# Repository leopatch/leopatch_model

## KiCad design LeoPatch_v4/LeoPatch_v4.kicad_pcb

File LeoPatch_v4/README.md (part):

# LeoPatch v4 – PCB (KiCad 9)

Newborn CCHD ECG screening board with **two ECG front ends side by side**, so they can be compared on the same hardware: the MAX30003 (digital, SPI) from v3 and the AD8232 (analog, SparkFun circuit) from v2. Each chip has its **own electrode jack**. Plug the lead cable into the jack of the chip you want to test. Do not put two sets of electrodes from both jacks on the same baby at once: the AD8232 drives RL, and the two input circuits would load each other.

4-layer, **70 × 71 mm** (v3 was 70 × 45; the board grew 26 mm at the bottom to make room for the AD8232 block and its jack). Top edge has the 20 × 6.6 mm cut-out under the module's antenna.

- **MCU:** Fanstel BM20BC module (nRF54LM20B + Axon NPU, BLE, 32 MHz and 32.768 kHz crystals built in). Its antenna hangs over the cut-out in the top edge. Keep the battery pack, cables and other metal away from that edge (Fanstel: 30 mm for best range)
- **ECG front end A – MAX30003 (U201, sheet "ECG front end"):** two-electrode lead I (ECGP = LA, ECGN = RA), 1.8 V from U202 (MCP1700T-1802E/TT in v4: the MCP1703AT-1802E/CB had 3 pcs at LCSC; same SOT-23 pinout), 32.768 kHz clock from X201, SPI to the module. Jack **J201 on the left edge** (plug goes in from the left), backup solder header J202. Silkscreen "MAX30003"
  - Input network matches Analog Devices' MAX30003WING2 evaluation kit (checked against it and the MAX30003 datasheet Rev 3): R201 / R202 49.9 kΩ pulse-proof 1206 (eval kit R4/R5 49.9k; Vishay CRCW…HP), C201 1 nF C0G across ECGP–ECGN (eval kit C10), C213 / C214 10 pF C0G from each input to GND (eval kit C8/C11), R208 499 kΩ from VCM to the RL electrode (eval kit R6: biases the baby at the chip's mid-voltage)
  - C202 (CAPP–CAPN) is 1 µF X7R: 0.5 Hz analog high-pass (datasheet default and eval kit C9), settles in ~1–2 s after the electrodes go on – fits the 2–5 s recordings
  - Firmware must close the input switches (clear OPENP / OPENN in CNFG_EMUX, they power up open). Internal lead bias (EN_RBIAS) is optional now that R208 drives RL from VCM; try with and without. SPI mode 0 or 3, ≤ 12 MHz. The part is rated 0–70 °C
- **ECG front end B – AD8232 (U601, sheet "ECG AD8232"):** the v2 circuit (SparkFun SEN-12650 / AD8232 datasheet Fig. 66 with a wider filter): band 0.5 Hz – ~145 Hz, gain ~200, clips at about ±7.8 mV at the electrodes. Jack **J601 on the bottom edge**, backup header J602, test pad TP601 ("ECG") on the op-amp output. Silkscreen "AD8232". Checked against the AD8232 datasheet (Rev D) in v4: R603 / R604 are 360 kΩ (patient current < 10 µA even in a fault: R ≥ 3.3 V / 10 µA, p. 21 and 26; was 180 k), and the output goes OUT → R623 1 kΩ → ECG_OUT with C608 10 nF to GND (p. 26 Fig. 61: the slow op amp needs a charge reservoir for the nRF54 ADC). SDN is only pulled up (R615): the AD8232 is always on. The reference (REFIN, 10 M / 10 M / 100 nF) takes ~2.5 s to settle after power-up
- Both jacks: 3.5 mm TRS, Tip = RL, Ring = LA, Sleeve = RA (same cable for both). Headers: pin 1 RL, 2 LA, 3 RA
- **External flash:** GD25WQ64ESIGR 8 MB SPI/QSPI NOR (U2, C4) on P2.00–P2.05, same pins as the nRF54LM20 DK flash. R2 (100 k) pulls FLASH_CS high. **v4 fix:** this part number is the 208-mil SOP-8 (the S in ESIGR); v2/v3 had a 150-mil SOIC-8 footprint it would not fit. U2 now uses SOIC-8 5.3 × 5.3 mm
- **Power:** 4×AA → on/off → BAT54J → MCP1703A 3.3 V LDO; USB-C 5 V also feeds the LDO through D102. Alligator-clip pins J103 **VIN** (3.6–6 V after the diodes, bypasses the on/off switch), J104 **3V3** (to feed 3.3 V in from a bench supply, or to measure current across JP101, desolder R101 first: R101 0 Ω is in parallel with JP101 and links the regulator to the 3.3 V rail), J105 **GND**
- **USB-C:** USB 2.0 device to the nRF54LM20B (firmware updates after the bootloader is flashed, data export, 5 V power). D+/D- top layer only, length-matched
- **UI:** PASS / CHECK / FAIL LEDs (green / yellow / red), START and EXPORT buttons, small RESET button (SW303). R301 (green LED) is 100 Ω: a green InGaN LED needs ~3 V, so 1 k from a 3.3 V pin gave only ~0.2 mA
- **Status LEDs (v4):** D103 **PWR** (green, on whenever the 3.3 V rail is up, ~0.5 mA) next to the 3V3 pin; a **LEADS ON** panel bottom right with D201 (MAX30003) and D601 (AD8232), green, active high. Firmware lights D201 while the MAX30003 reports no lead-off (DCLOFFINT clear) and D601 while the AD8232's LO+ and LO- are both low. The jacks have no plug-detect contact, so "leads on" (both electrodes touching skin) is what can be shown. Heartbeat LEDs did not fit: these used the last module pins that can still be routed out
- **Mounting:** five M2 holes (2.2 mm, not plated): H1 (104.0, 124.5), H2 (125.5, 112.0), H3 (167.5, 120.0), H4 (166.0, 167.0), H5 (104.0, 147.5) mm in board coordinates; top-left corner is (100, 100), y grows downward. Use nylon screws if range matters
- **Test points** (bare top-side pads, not in the BOM, silk-labelled): TP1 GND, TP2 +3V3, TP601 "ECG" = AD8232 output before its RC filter; TP202–TP206 "CS SCK MOSI MISO INT" = MAX30003 SPI bus (logic analyzer), TP201 "FCLK" = 32 kHz clock from X201, TP207 "1V8" = U202 output (MAX30003 DVDD); TP602 "ADC" = ECG_OUT after R623/C608 (what the nRF54 ADC sees) with TP604 "GND" beside it for the scope ground; TP603 "REF" = AD8232 REFOUT (~1.65 V); TP101 "VSNS" = battery divider. No test points on ECGP/ECGN, INP/INN or chip-side LA/RA (high impedance: a pad adds leakage and pickup); inject test signals at J202 / J602. Schematic: layout/fix_v4_testpoints_sch.py
- **Programming:** first flash (MCUboot) through J301, the 10-pin SWD header, from the nRF54LM20 DK "Debug out"; after that, update over USB-C or BLE

> Safety: do not connect USB to a mains-powered computer while electrodes are on a patient.

## Audio jacks and 3D models
- **J201 / J601 are CUI (Same Sky) SJ-3523-SMT-TR**, KiCad stock footprint `Connector_Audio:Jack_3.5mm_CUI_SJ-3523-SMT_Horizontal`. The barrel is at the footprint's -y end, so J201 is at 90° (plug from the left edge) and J601 at 180° (plug from the bottom edge), barrel tip flush with the edge. **v2, v3 and v4 before 2026-11-13 had both jacks backwards** (barrel facing into the board, body hanging off the edge): a plug could not go in.
- 3D models are project-relative (`${KIPRJMOD}/3d/...`), set by `layout/set_3d_models.py` (run by `build_all.sh`). `3d/bm20bc.step` is in git. `3d/SJ-3523-SMT-TR.step` is **not** in git (`.gitignore`), because the SamacSys licence forbids redistributing it outside your organisation and this repo is public. To see the jacks in 3D, download the SJ-3523-SMT-TR library from samesky.com (or componentsearchengine.com), then copy `3D/SJ-3523-SMT-TR.stp` to `LeoPatch_v4/3d/SJ-3523-SMT-TR.step`. Without it the jacks just render as footprints; the gerbers are unaffected.

## Firmware pin map (BM20BC pad → GPIO → net)
| Pad | GPIO | Net |
|---|---|---|
| E9 | P1.16 | ECG_SCK (MAX30003 SCLK) |
| K8 | P1.06 | ECG_MOSI (MAX30003 SDI) |
| A8 | P1.02 | ECG_MISO (MAX30003 SDO) – P1.02 is also the NFC2 pin: configure the NFC pins as GPIOs in firmware |
| D9 | P0.05 | ECG_CS (MAX30003 CSB) |
| C9 | P3.07 | ECG_INT (MAX30003 INTB, active low, 100 k pull-up R205) |
| F7 | P1.29 / **AIN3** | ECG_OUT (AD8232 output through R623 1 k / C608 10 nF, analog) |
| D8 | P3.06 | ECG_LO+ (AD8232 lead-off) |
| E8 | P1.25 | ECG_LO- (AD8232 lead-off) |
| A7 | P3.03 | LED_MAX_LEADS (D201, MAX30003 LEADS ON, active high) |
| F8 | P1.17 | LED_AD_LEADS (D601, AD8232 LEADS ON, active high) |
| K9 | P1.31 / AIN1 | VBAT_SENSE (VBAT × 0.248) |
| F9 / G9 | P1.18 / P1.19 | LED green / yellow (active high) |
| K2 | P3.10 | LED red (active high) |
| H9 | P1.09 | BTN_START (to GND, use internal pull-up) |
| J9 | P1.26 | BTN_EXPORT (to GND, use internal pull-up) |
| G6 / G7 / H7 | USB D- / D+ / VBUS | USB-C |
| K3 / J3 / G2 | SWDCLK / SWDIO / RESET | J301 |
| B2 | P2.01 | FLASH_SCK |
| B6 | P2.05 | FLASH_CS |
| E2 | P2.02 | FLASH_IO0 (MOSI) |
| B5 | P2.04 | FLASH_IO1 (MISO) |
| B4 | P2.03 | FLASH_IO2 (WP#) – drive high in plain SPI mode |
| B3 | P2.00 | FLASH_IO3 (HOLD#) – drive high in plain SPI mode |

nRF54LM20 analog inputs (from Nordic's SDK, `nrfx_soc_defines.h`; the Fanstel datasheet only lists AIN numbers for the BM15 module): AIN0 P1.00, AIN1 P1.31, AIN2 P1.30, AIN3 P1.29, AIN4 P1.06, AIN5 P1.05, AIN6 P1.04, AIN7 P1.03. The DK firmware reads AIN6 (P1.04); on this board the AD8232 output is **AIN3**.

Firmware notes for comparing the two chips:
- Sample the AD8232 at 1 kHz or more and notch mains hum in firmware, as in v2. Its output runs next to the MAX30003 SPI lines for part of the way, so do not clock the MAX30003 SPI while you sample the AD8232 (read one chip at a time).
- The AD8232 is always powered (SDN tied high); the MAX30003 can stay in its power-down state while you test the AD8232.
- Free module pads: only A5 (P0.00) and G8 (P1.08) are still unconnected, and with the current layout neither can be routed out without moving other tracks.

## Stackup
F.Cu signals + GND pour · In1 solid GND · In2 solid +3V3 · B.Cu signals + GND pour.
Tracks 0.2 mm (0.15 mm on every net that reaches the module, 0.3 mm on +1V8), clearance 0.15 mm, vias 0.45/0.3 mm (JLC standard "0.3mm/(0.4/0.45mm)" via option; set by layout/set_via_drill.py, order stackup JLC04161H-7628).
Vias are tented. None sits inside a pad except the ground vias in the exposed pads of the AD8232 and the MAX30003.
No vias and no new bottom-layer tracks under the module. Signals leave it on the top layer through the lanes between pads; the AD8232 lines leave through the lanes beside D9 / E9 / F9.

### Coupling check (`layout/check_coupling.py`, report in `layout/coupling_report.txt`)
Sensitive analog nets (ECG_OUT, all AD8232 nodes, MAX30003 inputs / references / +1V8, VBAT_SENSE) are kept at least 0.5 mm (edge to edge) from switching lines (MAX30003 SPI + INT, the 32 kHz FCLK, flash, USB, SWD) on the same layer; the router treats closer runs as expensive and routes in two passes so the early analog nets avoid where the digital lines go. F.Cu and B.Cu are shielded from each other by the two inner planes, so only same-layer neighbours count. What is left closer than 0.5 mm:
- ECG_OUT / ECG_SCK 1.9 mm at 0.25 mm – the module escape lanes (F7 sits next to E9), unavoidable; read one chip at a time anyway
- ECG_MOSI / VBAT_SENSE 1.1 mm at 0.46 mm on B.Cu at the module edge – VBAT_SENSE is a DC divider with 100 nF (C104); MOSI only toggles while configuring the MAX30003
- +1V8 / FCLK 0.1 mm at the MAX30003's neighbouring pins 13 / 14
Analog-to-analog neighbours inside each front end (e.g. LA next to RA, CAPP next to CAPN, the copied v2 AD8232 layout) are expected.
USB D+ / D-: top layer only, no vias, 16.02 / 15.92 mm, 0.27 mm wide, ~0.23 mm gap where coupled (~90 Ω differential on JLC04161H-7628).

## Folders
- `fab/` – Gerbers + drill (`LeoPatch_v4_gerbers.zip`, also unzipped in `gerbers/`) and the JLCPCB assembly files:
  - `LeoPatch_v4_JLC_BOM.csv` – Comment (part description + MPN), Designator, Footprint, LCSC Part #, Manufacturer, MPN, Quantity
  - `LeoPatch_v4_JLC_CPL.csv` – Designator, Mid X, Mid Y, Layer, Rotation (JLC rotation corrections applied, `layout/jlc_rotations.csv`)
  - `LeoPatch_v4_BOM_detailed.csv` – the same parts for people, with datasheet links and sourcing notes
  - Parts with no LCSC stock (no LCSC number in the BOM): none now (see below) – use JLC Global Sourcing or buy them (DigiKey/Mouser) and consign. JP101 needs no jumper cap (R101 0 Ω already links the regulator to the 3.3 V rail). The through-hole headers (J101, J103–J105, J202, J602, JP101) can be left out of the order and hand-soldered
  - **U1, U201 and J201/J601 come through JLC Global Sourcing** (LCSC C55288626 BM20BC from DigiKey, C5354728 MAX30003CTI+T from Mouser, C4991872 SJ-3523-SMT-TR from DigiKey; 10–20 business days). Order 5 / 5 / 10 for 5 boards. Pin headers / JST are moved to their body centre and the 1xN headers turned 90° in the CPL for JLC; 0603 LEDs turned 180°.
  - **X201 is a Micro Crystal OV-7604-C7** (LCSC C5337982, in stock, 0.5 µA): it replaced the Epson SG-3030CM (Global Sourcing minimum 808 pcs). Same land pattern, but pin 1 = CLKOUT and pin 3 = CLKOE (the Epson has them the other way round); the schematic symbol and board nets follow the OV-7604 (`layout/fix_v4_x201_sch.py`). Do not fit an SG-3030CM on v4.
  - Check every IC's pin-1 dot in JLC's placement preview before paying (rotation conventions differ between JLC library parts); J301, U2, U101, U102, U202, SW303 have corrections applied
- `docs/` – schematic PDF and top render
- `layout/` – scripts. v4 is built by `build_all.sh` (KiCad closed): it starts from `v4_start.kicad_pcb` (the v3 board), then
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
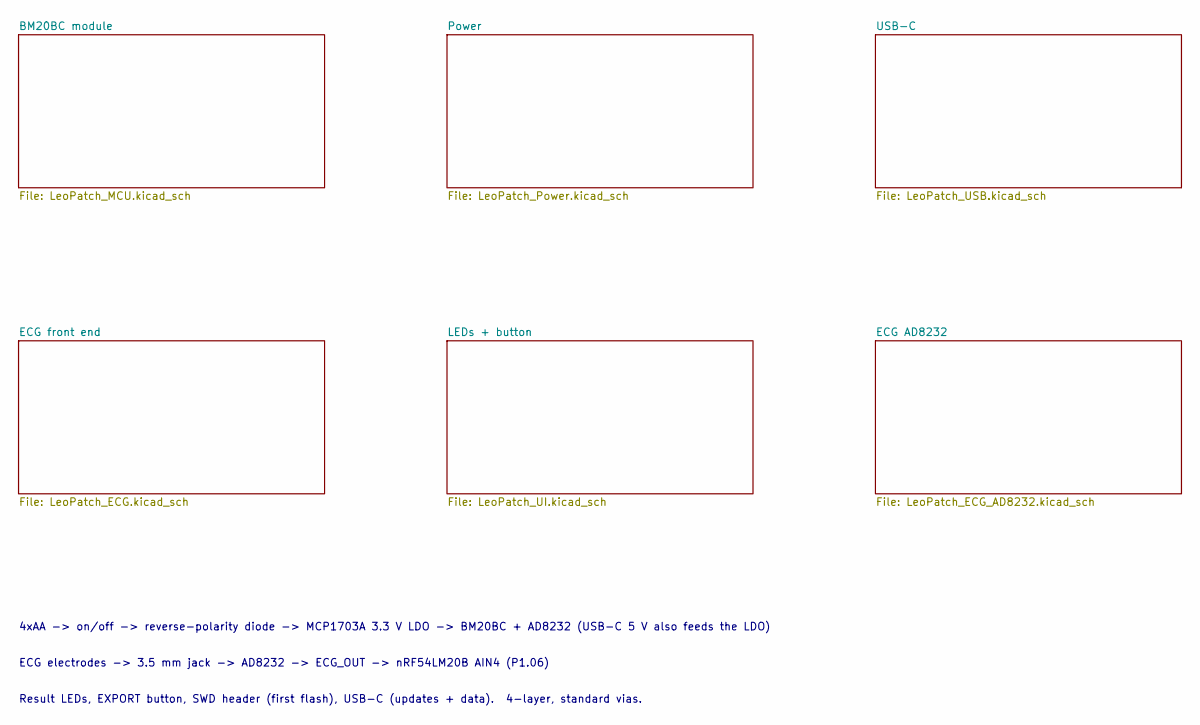
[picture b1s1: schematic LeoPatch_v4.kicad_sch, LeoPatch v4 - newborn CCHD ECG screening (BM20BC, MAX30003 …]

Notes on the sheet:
ECG electrodes -> 3.5 mm jack -> AD8232 -> ECG_OUT -> nRF54LM20B AIN4 (P1.06)
4xAA -> on/off -> reverse-polarity diode -> MCP1703A 3.3 V LDO -> BM20BC + AD8232 (USB-C 5 V also feeds the LDO)
Result LEDs, EXPORT button, SWD header (first flash), USB-C (updates + data). 4-layer, standard vias.

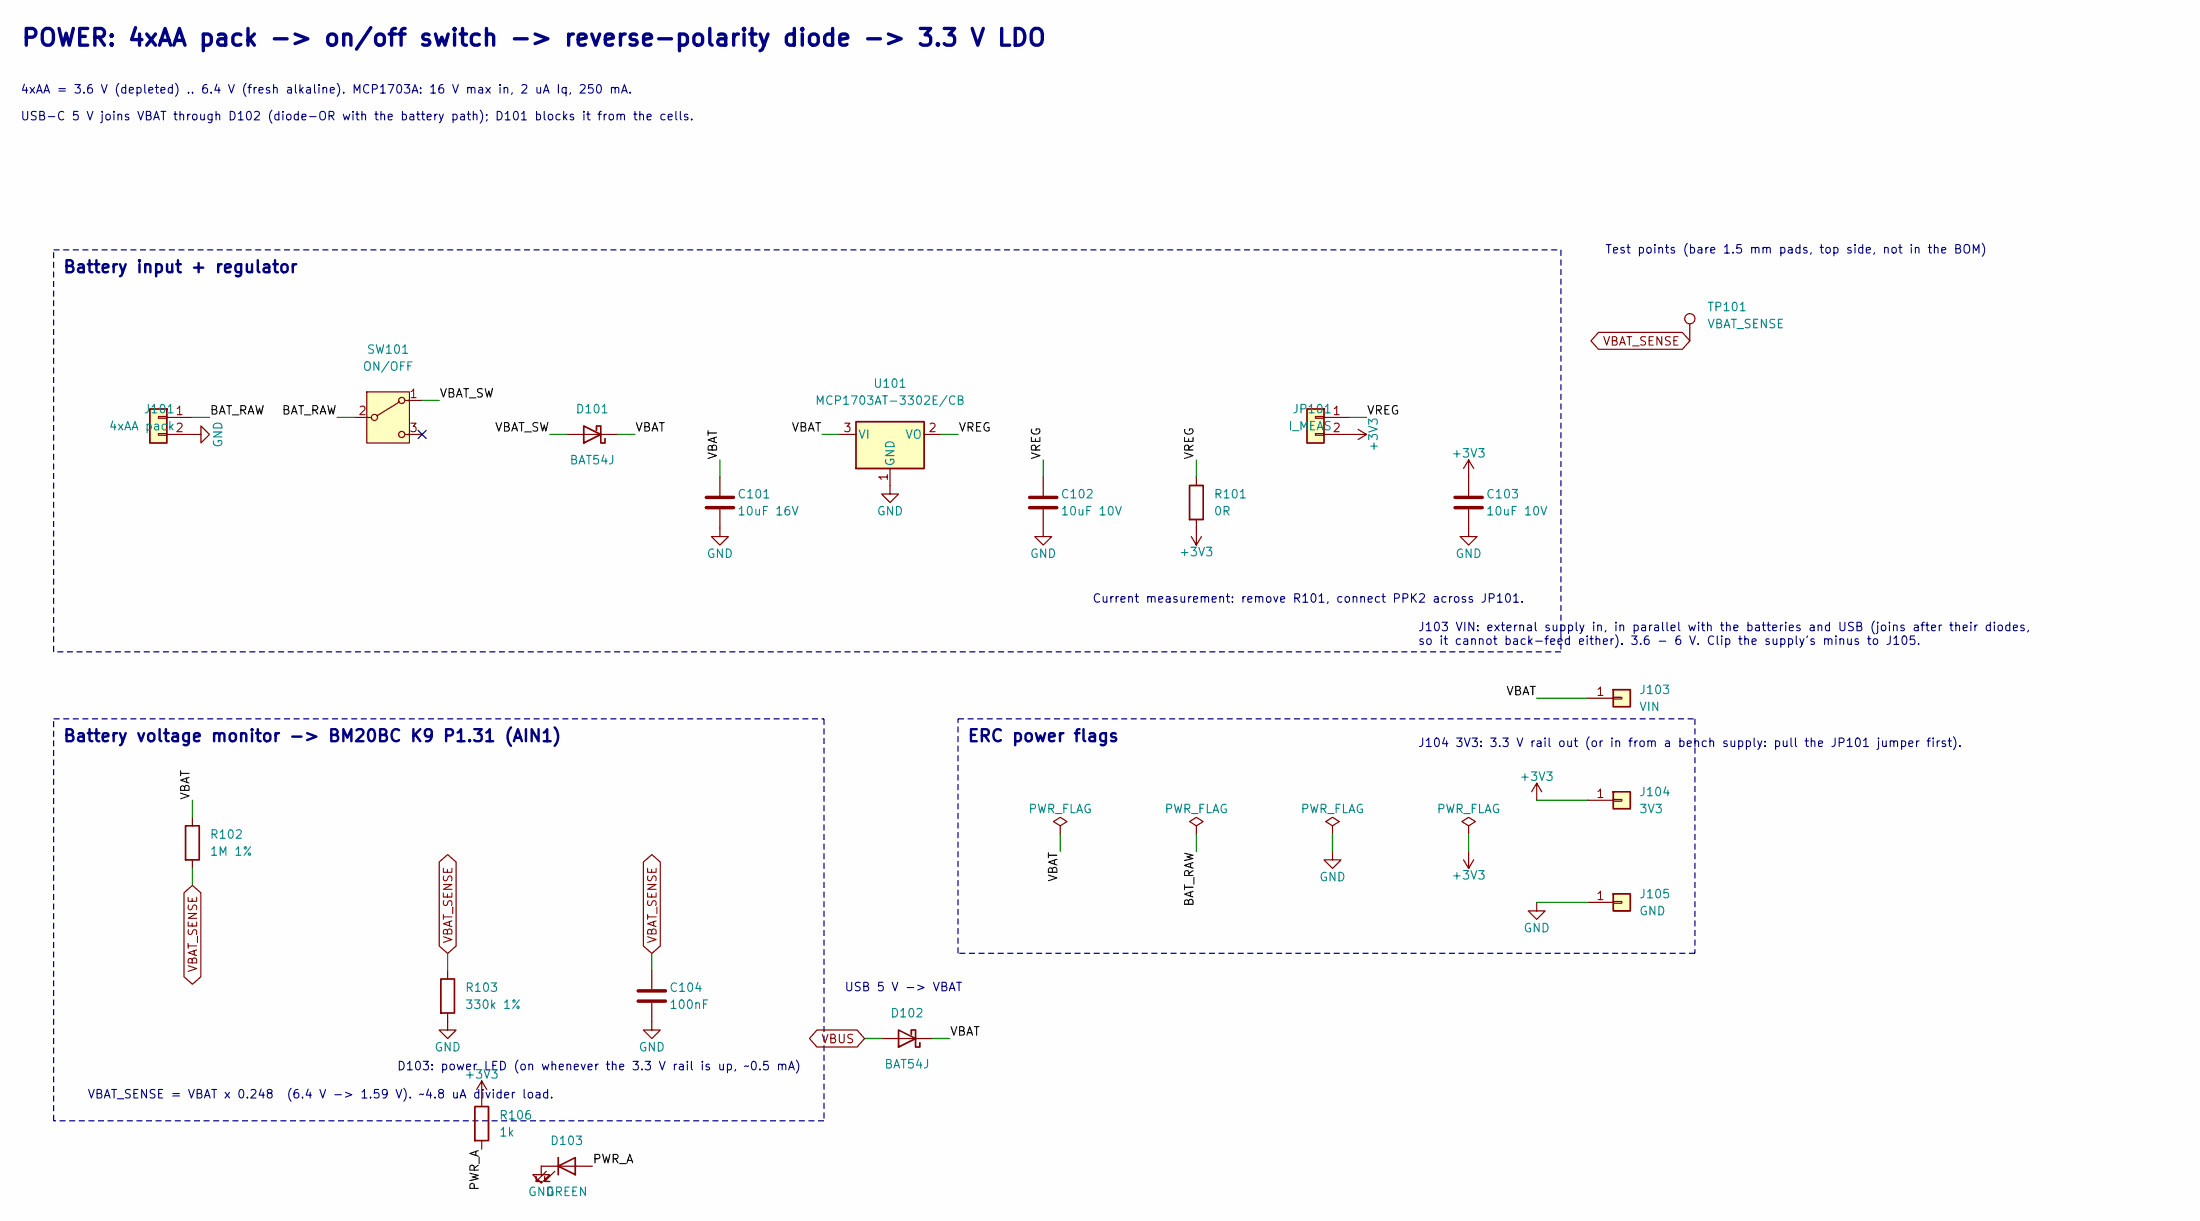
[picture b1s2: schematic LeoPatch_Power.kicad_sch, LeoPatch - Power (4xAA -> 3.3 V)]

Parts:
C101: 10uF 16V; C_0805_2012Metric; MPN CL21A106KAYNNNE; LCSC C15850
C102, C103: 10uF 10V; C_0805_2012Metric; MPN CL21A106KAYNNNE; LCSC C15850
C104: 100nF; C_0603_1608Metric; MPN CC0603KRX7R9BB104; LCSC C14663
D101, D102: BAT54J; D_SOD-323; MPN BAT54JFILM; LCSC C86299
D103: GREEN; LED_0603_1608Metric; MPN KT-0603G; LCSC C12624
J101: 4xAA pack; JST_PH_B2B-PH-K_1x02_P2.00mm_Vertical; MPN B2B-PH-K-S(LF)(SN); LCSC C131337
J103: VIN; PinHeader_1x01_P2.54mm_Vertical; MPN PZ254V-11-01P; LCSC C492400
J104: 3V3; PinHeader_1x01_P2.54mm_Vertical; MPN PZ254V-11-01P; LCSC C492400
J105: GND; PinHeader_1x01_P2.54mm_Vertical; MPN PZ254V-11-01P; LCSC C492400
JP101: I_MEAS; PinHeader_1x02_P2.54mm_Vertical; MPN PZ254V-11-02P; LCSC C492401
R101: 0R; R_0603_1608Metric; MPN 0603WAF0000T5E; LCSC C21189
R102: 1M 1%; R_0603_1608Metric; MPN 0603WAF1004T5E; LCSC C22935
R103: 330k 1%; R_0603_1608Metric; MPN 0603WAF3303T5E; LCSC C23137
R106: 1k; R_0603_1608Metric; MPN 0603WAF1001T5E; LCSC C21190
SW101: ON/OFF; SW_SPDT_PCM12; MPN PCM12SMTR; LCSC C221841
TP101: VBAT_SENSE; TestPoint_Pad_D1.5mm
U101: MCP1703AT-3302E/CB; SOT-23; MPN MCP1703AT-3302E/CB; LCSC C144183

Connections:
+3V3: C103.1, J104.1, JP101.2, R101.2, R106.1; also elsewhere on the board
/Power/BAT_RAW: J101.1, SW101.2 (B)
/Power/PWR_A: D103.2 (A), R106.2
/Power/VBAT: C101.1, D101.1 (K), D102.1 (K), J103.1, R102.1, U101.3 (VI)
/Power/VBAT_SW: D101.2 (A), SW101.1 (A)
/Power/VREG: C102.1, JP101.1, R101.1, U101.2 (VO)
GND: C101.2, C102.2, C103.2, C104.2, D103.1 (K), J101.2, J105.1, R103.2, U101.1 (GND); also elsewhere on the board
VBAT_SENSE: C104.1, R102.2, R103.1, TP101.1; also elsewhere on the board
VBUS: D102.2 (A); also elsewhere on the board

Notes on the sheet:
Battery voltage monitor -> BM20BC K9 P1.31 (AIN1)
4xAA = 3.6 V (depleted) .. 6.4 V (fresh alkaline). MCP1703A: 16 V max in, 2 uA Iq, 250 mA.
ERC power flags
J103 VIN: external supply in, in parallel with the batteries and USB (joins after their diodes, so it cannot back-feed either). 3.6 - 6 V. Clip the supply's minus to J105.
USB-C 5 V joins VBAT through D102 (diode-OR with the battery path); D101 blocks it from the cells.
Current measurement: remove R101, connect PPK2 across JP101.
VBAT_SENSE = VBAT x 0.248 (6.4 V -> 1.59 V). ~4.8 uA divider load.
POWER: 4xAA pack -> on/off switch -> reverse-polarity diode -> 3.3 V LDO
D103: power LED (on whenever the 3.3 V rail is up, ~0.5 mA)
Battery input + regulator
Test points (bare 1.5 mm pads, top side, not in the BOM)
J104 3V3: 3.3 V rail out (or in from a bench supply: pull the JP101 jumper first).
USB 5 V -> VBAT

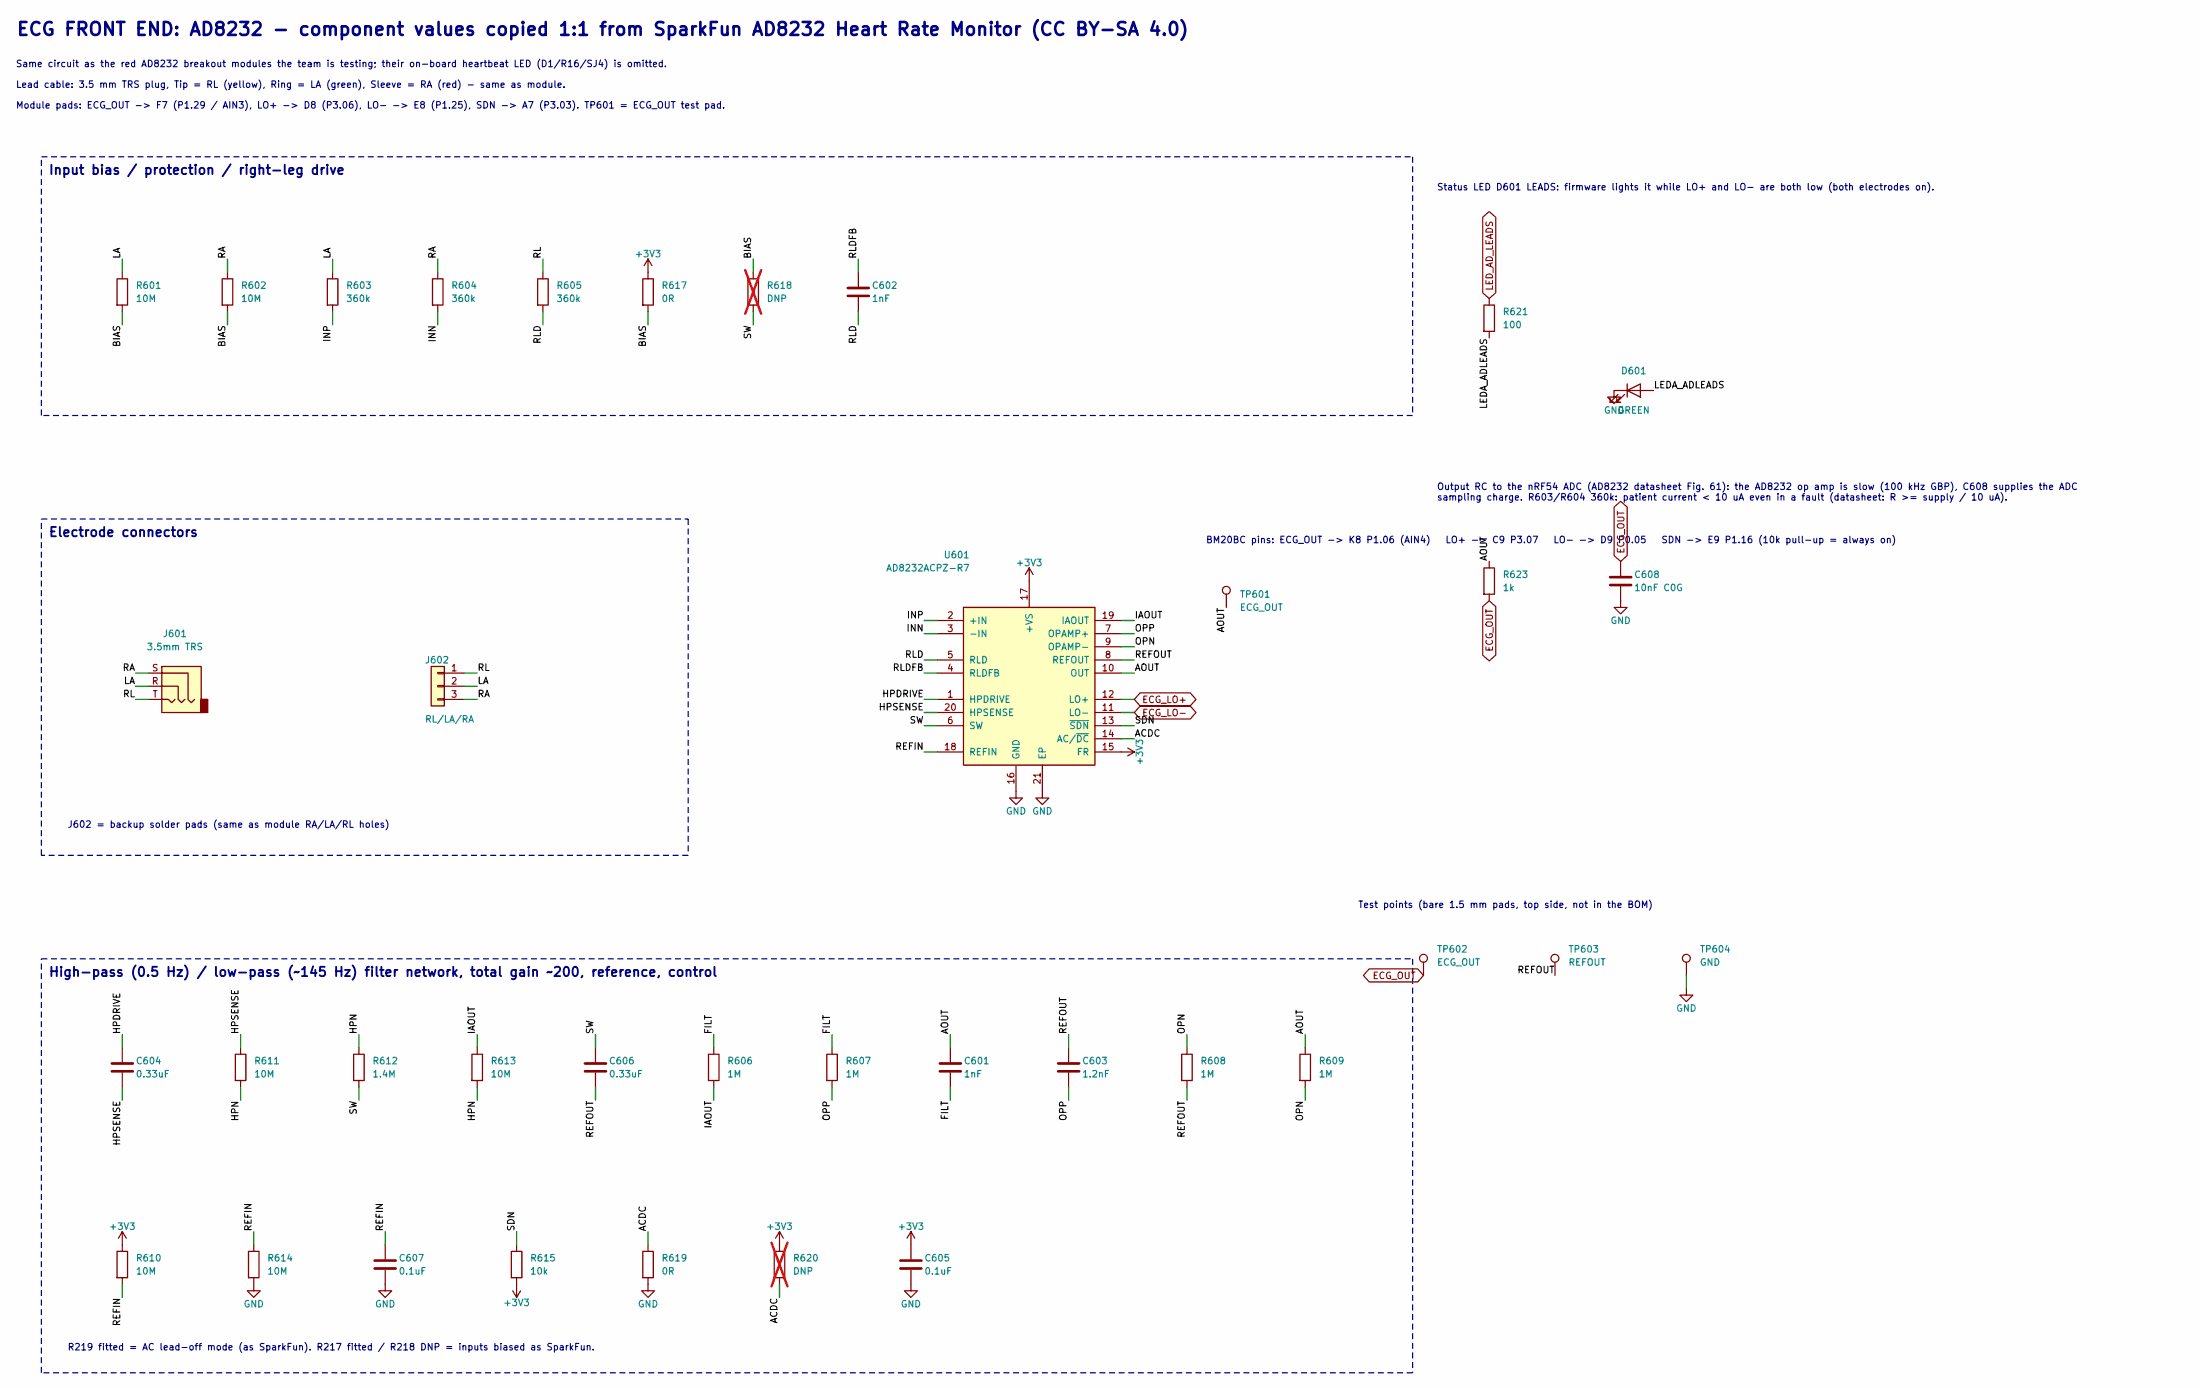
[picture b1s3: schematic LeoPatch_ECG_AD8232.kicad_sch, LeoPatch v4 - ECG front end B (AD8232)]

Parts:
C601, C602: 1nF; C_0603_1608Metric; MPN CL10C102JB8NNNC; LCSC C163508
C603: 1.2nF; C_0603_1608Metric; MPN 0603CG122J500NT; LCSC C68659
C604, C606: 0.33uF; C_0805_2012Metric; MPN CC0805KKX7R9BB334; LCSC C107132
C605, C607: 0.1uF; C_0603_1608Metric; MPN CC0603KRX7R9BB104; LCSC C14663
C608: 10nF C0G; C_0603_1608Metric; MPN GRM1885C1H103JA01D; LCSC C85973
D601: GREEN; LED_0603_1608Metric; MPN KT-0603G; LCSC C12624
J601: 3.5mm TRS; Jack_3.5mm_CUI_SJ-3523-SMT_Horizontal; MPN SJ-3523-SMT-TR; LCSC C4991872
J602: RL/LA/RA; PinHeader_1x03_P2.54mm_Vertical; MPN PZ254V-11-03P; LCSC C2937625
R601, R602, R610, R611, R613, R614: 10M; R_0603_1608Metric; MPN 0603WAF1005T5E; LCSC C7250
R603, R604, R605: 360k; R_0603_1608Metric; MPN 0603WAF3603T5E; LCSC C23146
R606, R607, R608, R609: 1M; R_0603_1608Metric; MPN 0603WAF1004T5E; LCSC C22935
R612: 1.4M; R_0603_1608Metric; MPN 0603WAF1404T5E; LCSC C38070
R615: 10k; R_0603_1608Metric; MPN 0603WAF1002T5E; LCSC C25804
R617, R619: 0R; R_0603_1608Metric; MPN 0603WAF0000T5E; LCSC C21189
R618, R620: DNP; R_0603_1608Metric; not fitted
R621: 100; R_0603_1608Metric; MPN 0603WAF1000T5E; LCSC C22775
R623: 1k; R_0603_1608Metric; MPN 0603WAF1001T5E; LCSC C21190
TP601: ECG_OUT; TestPoint_Pad_D1.0mm
TP602: ECG_OUT; TestPoint_Pad_D1.5mm
TP603: REFOUT; TestPoint_Pad_D1.5mm
TP604: GND; TestPoint_Pad_D1.5mm
U601: AD8232ACPZ-R7; LFCSP-20-1EP_4x4mm_P0.5mm_EP2.5x2.5mm; MPN AD8232ACPZ-R7; LCSC C43216

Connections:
+3V3: C605.1, R610.1, R615.2, R617.1, R620.1, U601.15 (FR), U601.17 (+VS); also elsewhere on the board
/ECG AD8232/ACDC: R619.1, R620.2, U601.14 (AC/~DC)
/ECG AD8232/AOUT: C601.1, R609.1, R623.1, TP601.1, U601.10 (OUT)
/ECG AD8232/BIAS: R601.2, R602.2, R617.2, R618.1
/ECG AD8232/FILT: C601.2, R606.1, R607.1
/ECG AD8232/HPDRIVE: C604.1, U601.1 (HPDRIVE)
/ECG AD8232/HPN: R611.2, R612.1, R613.2
/ECG AD8232/HPSENSE: C604.2, R611.1, U601.20 (HPSENSE)
/ECG AD8232/IAOUT: R606.2, R613.1, U601.19 (IAOUT)
/ECG AD8232/INN: R604.2, U601.3 (-IN)
/ECG AD8232/INP: R603.2, U601.2 (+IN)
/ECG AD8232/LA: J601.R, J602.2, R601.1, R603.1
/ECG AD8232/LEDA_ADLEADS: D601.2 (A), R621.2
/ECG AD8232/OPN: R608.1, R609.2, U601.9 (OPAMP-)
/ECG AD8232/OPP: C603.2, R607.2, U601.7 (OPAMP+)
/ECG AD8232/RA: J601.S, J602.3, R602.1, R604.1
/ECG AD8232/REFIN: C607.1, R610.2, R614.1, U601.18 (REFIN)
/ECG AD8232/REFOUT: C603.1, C606.2, R608.2, TP603.1, U601.8 (REFOUT)
/ECG AD8232/RL: J601.T, J602.1, R605.1
/ECG AD8232/RLD: C602.2, R605.2, U601.5 (RLD)
/ECG AD8232/RLDFB: C602.1, U601.4 (RLDFB)
/ECG AD8232/SDN: R615.1, U601.13 (~SDN)
/ECG AD8232/SW: C606.1, R612.2, R618.2, U601.6 (SW)
ECG_LO+: U601.12 (LO+); also elsewhere on the board
ECG_LO-: U601.11 (LO-); also elsewhere on the board
ECG_OUT: C608.1, R623.2, TP602.1; also elsewhere on the board
GND: C605.2, C607.2, C608.2, D601.1 (K), R614.2, R619.2, TP604.1, U601.16 (GND), U601.21 (EP); also elsewhere on the board
LED_AD_LEADS: R621.1; also elsewhere on the board

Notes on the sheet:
BM20BC pins: ECG_OUT -> K8 P1.06 (AIN4) LO+ -> C9 P3.07 LO- -> D9 P0.05 SDN -> E9 P1.16 (10k pull-up = always on)
Input bias / protection / right-leg drive
Module pads: ECG_OUT -> F7 (P1.29 / AIN3), LO+ -> D8 (P3.06), LO- -> E8 (P1.25), SDN -> A7 (P3.03). TP601 = ECG_OUT test pad.
ECG FRONT END: AD8232 - component values copied 1:1 from SparkFun AD8232 Heart Rate Monitor (CC BY-SA 4.0)
Output RC to the nRF54 ADC (AD8232 datasheet Fig. 61): the AD8232 op amp is slow (100 kHz GBP), C608 supplies the ADC sampling charge. R603/R604 360k: patient current < 10 uA even in a fault (datasheet: R >= supply / 10 uA).
Same circuit as the red AD8232 breakout modules the team is testing; their on-board heartbeat LED (D1/R16/SJ4) is omitted.
Lead cable: 3.5 mm TRS plug, Tip = RL (yellow), Ring = LA (green), Sleeve = RA (red) - same as module.
Test points (bare 1.5 mm pads, top side, not in the BOM)
Electrode connectors
High-pass (0.5 Hz) / low-pass (~145 Hz) filter network, total gain ~200, reference, control
J602 = backup solder pads (same as module RA/LA/RL holes)
Status LED D601 LEADS: firmware lights it while LO+ and LO- are both low (both electrodes on).
R219 fitted = AC lead-off mode (as SparkFun). R217 fitted / R218 DNP = inputs biased as SparkFun.

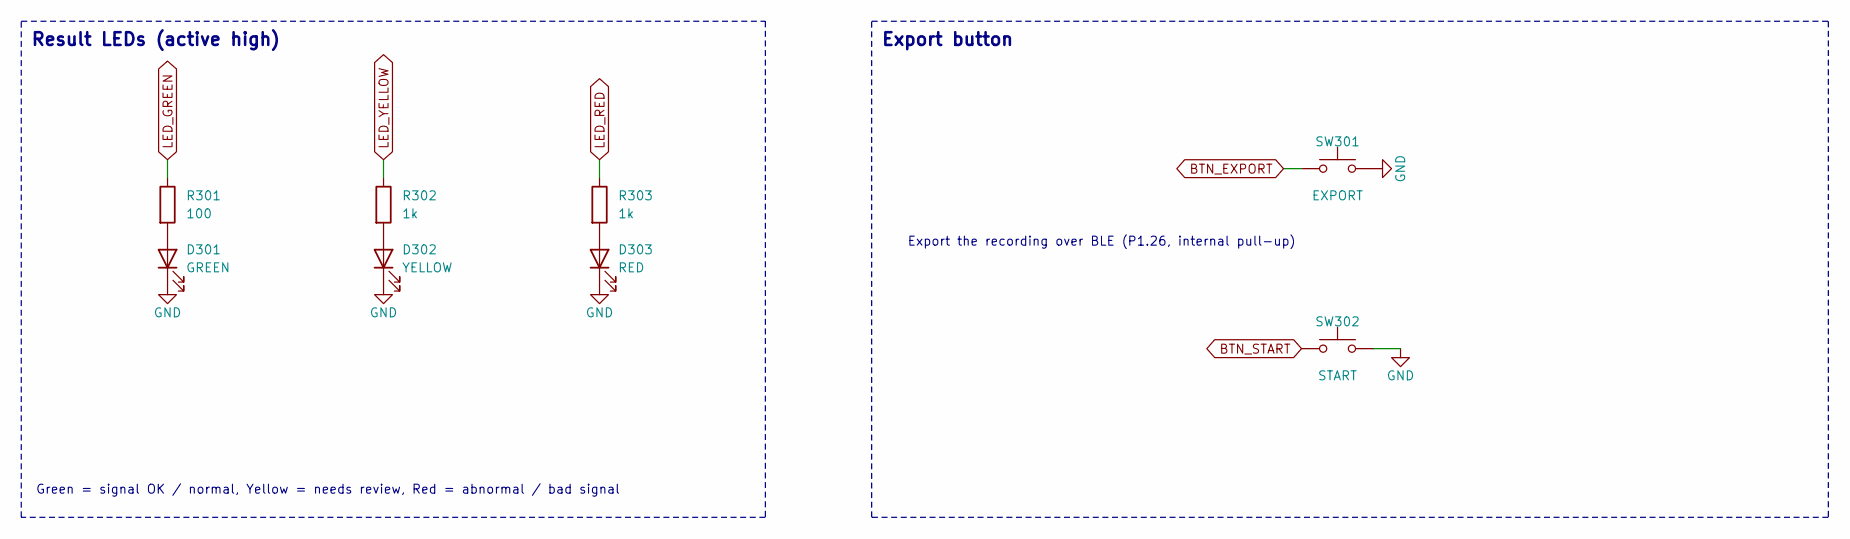
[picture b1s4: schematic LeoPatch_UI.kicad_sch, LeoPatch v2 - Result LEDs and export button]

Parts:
D301: GREEN; LED_0603_1608Metric; MPN KT-0603G; LCSC C12624
D302: YELLOW; LED_0603_1608Metric; MPN KT-0603Y; LCSC C2287
D303: RED; LED_0603_1608Metric; MPN KT-0603R; LCSC C2286
R301: 100; R_0603_1608Metric; MPN 0603WAF1000T5E; LCSC C22775
R302, R303: 1k; R_0603_1608Metric; MPN 0603WAF1001T5E; LCSC C21190
SW301: EXPORT; SW_SPST_PTS645Sx43SMTR92; MPN PTS645SM43SMTR92 LFS; LCSC C221880
SW302: START; SW_SPST_PTS645Sx43SMTR92; MPN PTS645SM43SMTR92 LFS; LCSC C221880

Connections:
BTN_EXPORT: SW301.1; also elsewhere on the board
BTN_START: SW302.1; also elsewhere on the board
GND: D301.1 (K), D302.1 (K), D303.1 (K), SW301.2, SW302.2; also elsewhere on the board
LED_GREEN: R301.1; also elsewhere on the board
LED_RED: R303.1; also elsewhere on the board
LED_YELLOW: R302.1; also elsewhere on the board
unnamed: D301.2 (A), R301.2
unnamed: D302.2 (A), R302.2
unnamed: D303.2 (A), R303.2

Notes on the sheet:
Result LEDs (active high)
Green = signal OK / normal, Yellow = needs review, Red = abnormal / bad signal
Export button
Export the recording over BLE (P1.26, internal pull-up)

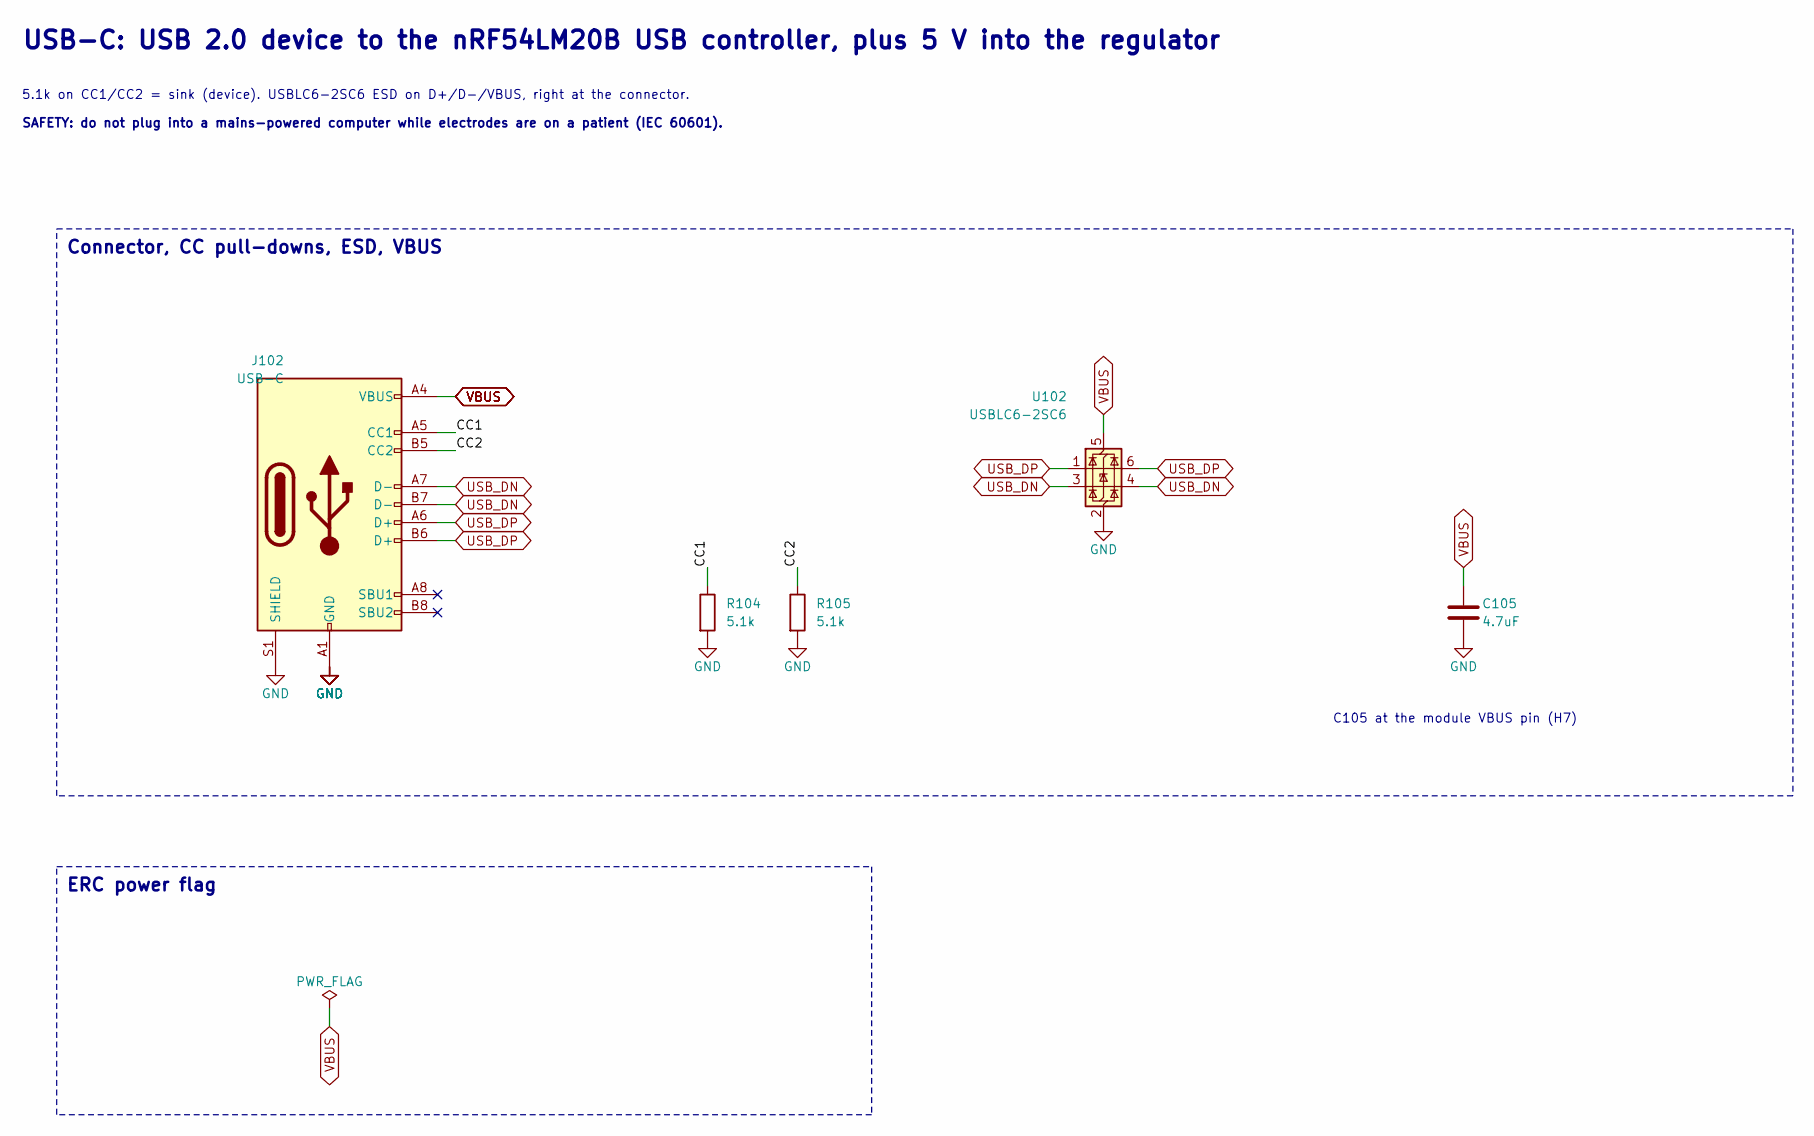
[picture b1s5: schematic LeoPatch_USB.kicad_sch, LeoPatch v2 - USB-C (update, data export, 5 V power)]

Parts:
C105: 4.7uF; C_0603_1608Metric; MPN CL10A475KO8NNNC; LCSC C19666
J102: USB-C; USB_C_Receptacle_GCT_USB4105-xx-A_16P_TopMnt_Horizontal; MPN USB4105-GF-A; LCSC C3020560
R104, R105: 5.1k; R_0603_1608Metric; MPN 0603WAF5101T5E; LCSC C23186
U102: USBLC6-2SC6; SOT-23-6; MPN USBLC6-2SC6; LCSC C7519

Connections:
/USB-C/CC1: J102.A5 (CC1), R104.1
/USB-C/CC2: J102.B5 (CC2), R105.1
GND: C105.2, J102.A1 (GND), J102.A12 (GND), J102.B1 (GND), J102.B12 (GND), J102.S1 (SHIELD), R104.2, R105.2, U102.2 (GND); also elsewhere on the board
USB_DN: J102.A7 (D-), J102.B7 (D-), U102.3 (I/O2), U102.4 (I/O2); also elsewhere on the board
USB_DP: J102.A6 (D+), J102.B6 (D+), U102.1 (I/O1), U102.6 (I/O1); also elsewhere on the board
VBUS: C105.1, J102.A4 (VBUS), J102.A9 (VBUS), J102.B4 (VBUS), J102.B9 (VBUS), U102.5 (VBUS); also elsewhere on the board

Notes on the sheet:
C105 at the module VBUS pin (H7)
5.1k on CC1/CC2 = sink (device). USBLC6-2SC6 ESD on D+/D-/VBUS, right at the connector.
SAFETY: do not plug into a mains-powered computer while electrodes are on a patient (IEC 60601).
ERC power flag
Connector, CC pull-downs, ESD, VBUS
USB-C: USB 2.0 device to the nRF54LM20B USB controller, plus 5 V into the regulator

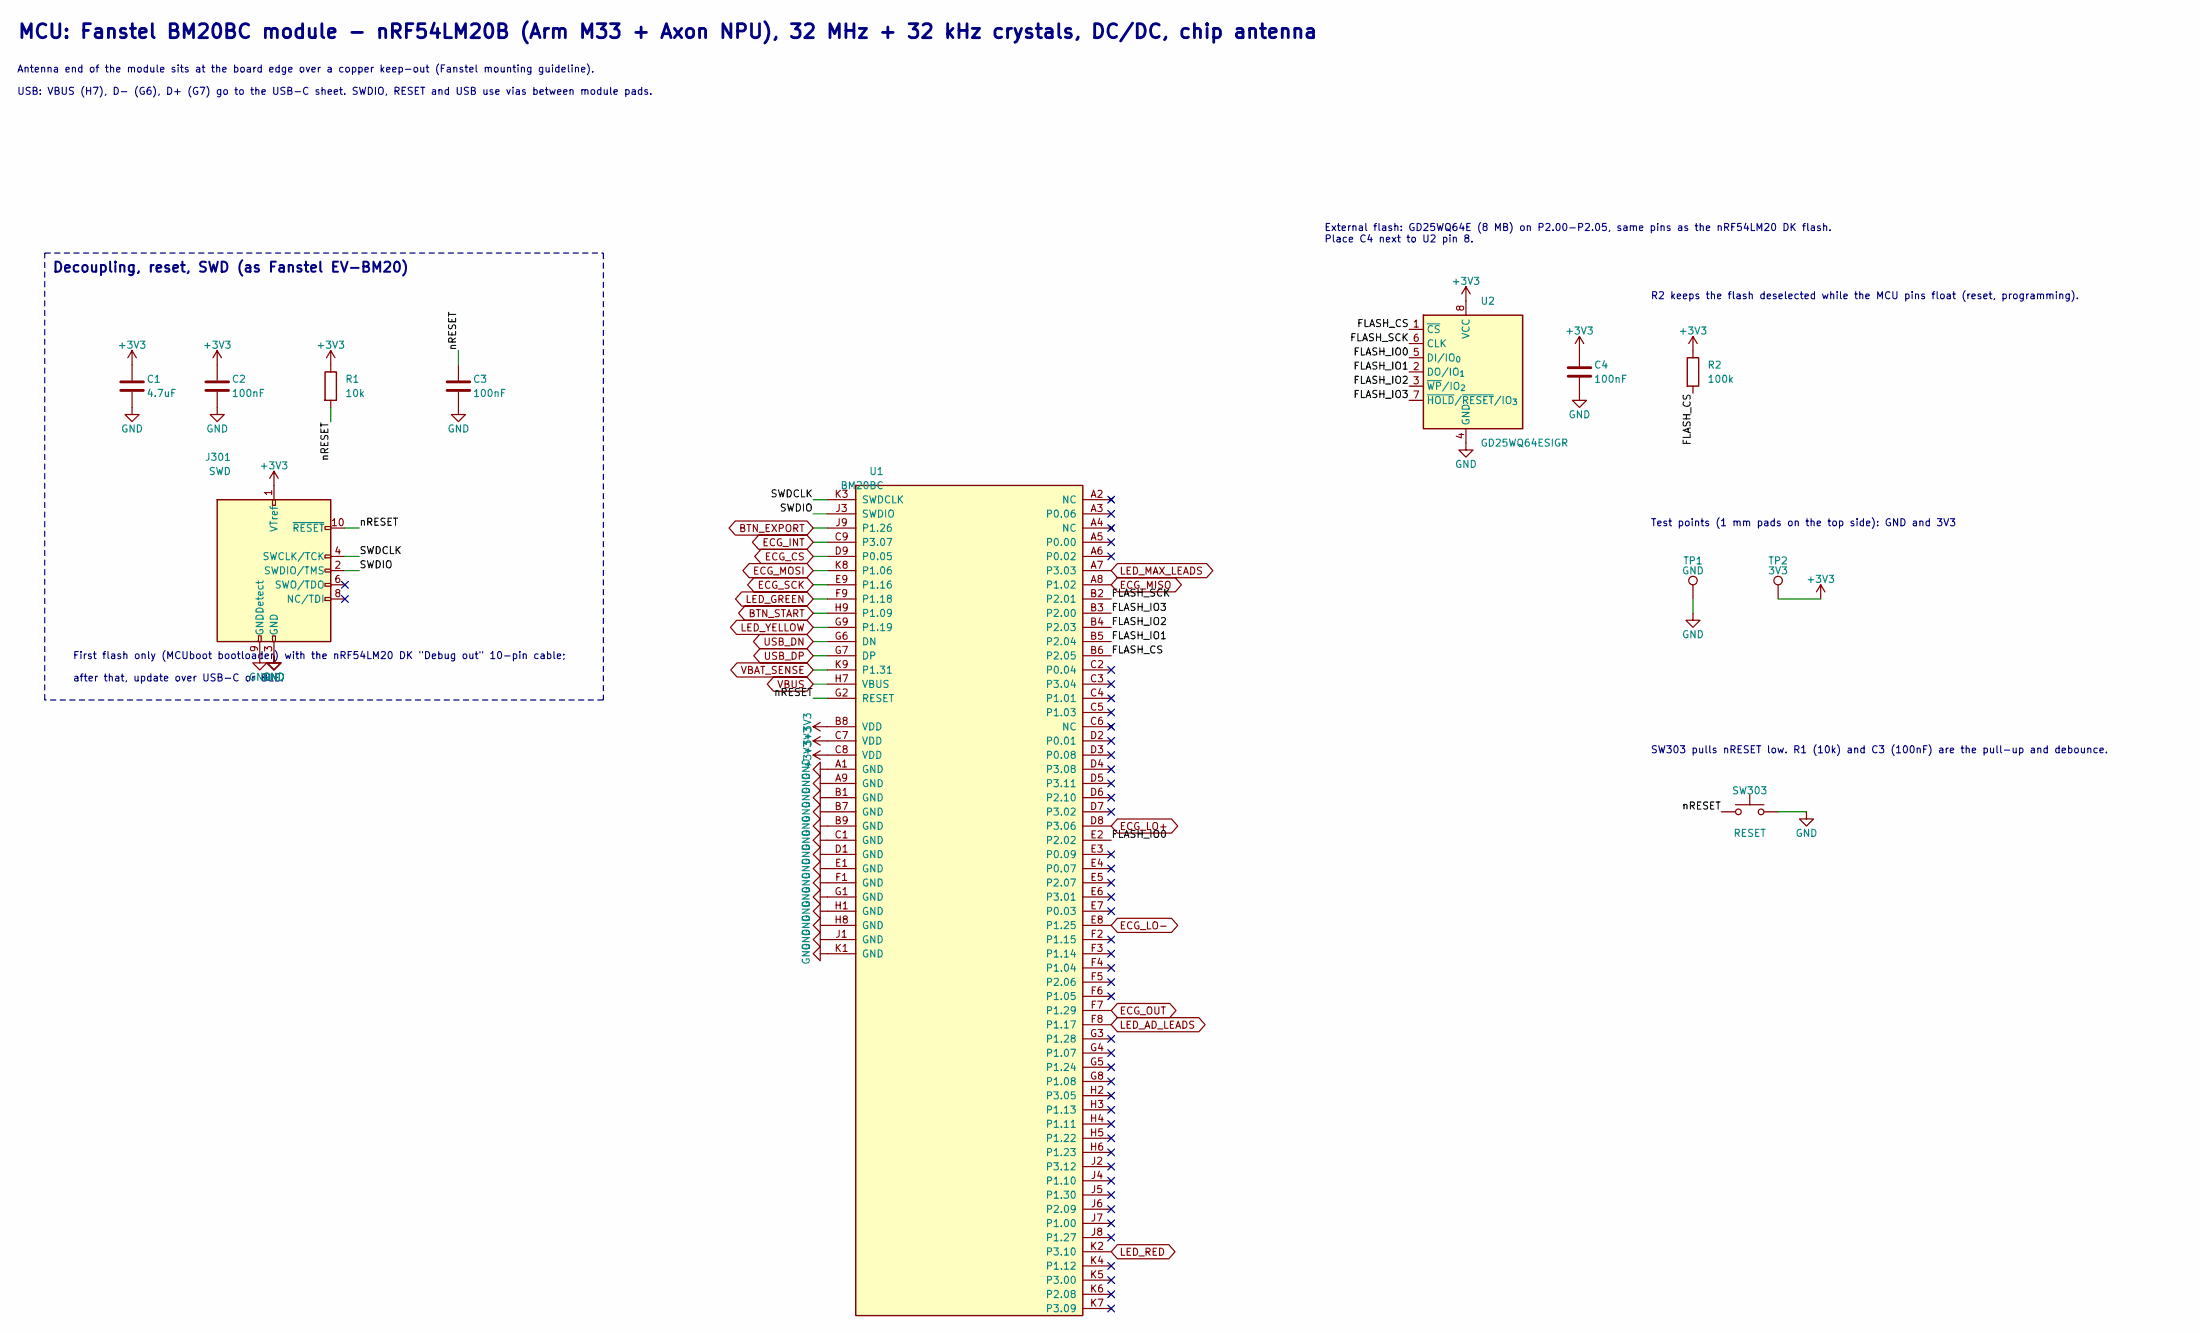
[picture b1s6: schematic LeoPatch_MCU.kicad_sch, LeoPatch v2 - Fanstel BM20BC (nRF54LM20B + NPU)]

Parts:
C1: 4.7uF; C_0603_1608Metric; MPN CL10A475KO8NNNC; LCSC C19666
C2, C3, C4: 100nF; C_0603_1608Metric; MPN CC0603KRX7R9BB104; LCSC C14663
J301: SWD; PinHeader_2x05_P1.27mm_Vertical_SMD; MPN HX PZ1.27-2x5P TP; LCSC C41376037
R1: 10k; R_0603_1608Metric; MPN 0603WAF1002T5E; LCSC C25804
R2: 100k; R_0603_1608Metric; MPN 0603WAF1003T5E; LCSC C25803
SW303: RESET; SW_SPST_B3U-1000P; MPN B3U-1000P; LCSC C231329
TP1: GND; TestPoint_Pad_D1.0mm
TP2: 3V3; TestPoint_Pad_D1.0mm
U1: BM20BC; Fanstel_BM20BC; MPN BM20BC; LCSC C55288626
U2: GD25WQ64ESIGR; SOIC-8_5.3x5.3mm_P1.27mm; MPN GD25WQ64ESIGR; LCSC C3202809

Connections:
+3V3: C1.1, C2.1, C4.1, J301.1 (VTref), R1.1, R2.1, TP2.1, U1.B8 (VDD), U1.C7 (VDD), U1.C8 (VDD), U2.8 (VCC); also elsewhere on the board
/BM20BC module/FLASH_CS: R2.2, U1.B6 (P2.05), U2.1 (~CS)
/BM20BC module/FLASH_IO0: U1.E2 (P2.02), U2.5 (DI/IO_{0})
/BM20BC module/FLASH_IO1: U1.B5 (P2.04), U2.2 (DO/IO_{1})
/BM20BC module/FLASH_IO2: U1.B4 (P2.03), U2.3 (~WP/IO_{2})
/BM20BC module/FLASH_IO3: U1.B3 (P2.00), U2.7 (~HOLD/~RESET/IO_{3})
/BM20BC module/FLASH_SCK: U1.B2 (P2.01), U2.6 (CLK)
/BM20BC module/SWDCLK: J301.4 (SWCLK/TCK), U1.K3 (SWDCLK)
/BM20BC module/SWDIO: J301.2 (SWDIO/TMS), U1.J3 (SWDIO)
/BM20BC module/nRESET: C3.1, J301.10 (~RESET), R1.2, SW303.1, U1.G2 (RESET)
BTN_EXPORT: U1.J9 (P1.26); also elsewhere on the board
BTN_START: U1.H9 (P1.09); also elsewhere on the board
ECG_CS: U1.D9 (P0.05); also elsewhere on the board
ECG_INT: U1.C9 (P3.07); also elsewhere on the board
ECG_LO+: U1.D8 (P3.06); also elsewhere on the board
ECG_LO-: U1.E8 (P1.25); also elsewhere on the board
ECG_MISO: U1.A8 (P1.02); also elsewhere on the board
ECG_MOSI: U1.K8 (P1.06); also elsewhere on the board
ECG_OUT: U1.F7 (P1.29); also elsewhere on the board
ECG_SCK: U1.E9 (P1.16); also elsewhere on the board
GND: C1.2, C2.2, C3.2, C4.2, J301.3 (GND), J301.5 (GND), J301.9 (GNDDetect), SW303.2, TP1.1, U1.A1 (GND), U1.A9 (GND), U1.B1 (GND), U1.B7 (GND), U1.B9 (GND), U1.C1 (GND), U1.D1 (GND), U1.E1 (GND), U1.F1 (GND), U1.G1 (GND), U1.H1 (GND), U1.H8 (GND), U1.J1 (GND), U1.K1 (GND), U2.4 (GND); also elsewhere on the board
LED_AD_LEADS: U1.F8 (P1.17); also elsewhere on the board
LED_GREEN: U1.F9 (P1.18); also elsewhere on the board
LED_MAX_LEADS: U1.A7 (P3.03); also elsewhere on the board
LED_RED: U1.K2 (P3.10); also elsewhere on the board
LED_YELLOW: U1.G9 (P1.19); also elsewhere on the board
USB_DN: U1.G6 (DN); also elsewhere on the board
USB_DP: U1.G7 (DP); also elsewhere on the board
VBAT_SENSE: U1.K9 (P1.31); also elsewhere on the board
VBUS: U1.H7 (VBUS); also elsewhere on the board

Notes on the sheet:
Decoupling, reset, SWD (as Fanstel EV-BM20)
First flash only (MCUboot bootloader) with the nRF54LM20 DK "Debug out" 10-pin cable;
Test points (1 mm pads on the top side): GND and 3V3
SW303 pulls nRESET low. R1 (10k) and C3 (100nF) are the pull-up and debounce.
External flash: GD25WQ64E (8 MB) on P2.00-P2.05, same pins as the nRF54LM20 DK flash. Place C4 next to U2 pin 8.
MCU: Fanstel BM20BC module - nRF54LM20B (Arm M33 + Axon NPU), 32 MHz + 32 kHz crystals, DC/DC, chip antenna
Antenna end of the module sits at the board edge over a copper keep-out (Fanstel mounting guideline).
after that, update over USB-C or BLE.
USB: VBUS (H7), D- (G6), D+ (G7) go to the USB-C sheet. SWDIO, RESET and USB use vias between module pads.
R2 keeps the flash deselected while the MCU pins float (reset, programming).
